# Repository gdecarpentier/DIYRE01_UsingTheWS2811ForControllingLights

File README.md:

# DIYRE01_UsingTheWS2811ForControllingLights

Repository of the free source code and schematics accompanying this YouTube video:

[DIY Railway Electronics # 01 - Using the WS2811 for controlling lights](https://www.youtube.com/watch?v=AYqMWdDcELc).

|Directory|Description|
|-|-|
| /ws2811_eagle | The EAGLE schematics and board files for the WS2811 board in the video. |
| /ws2811_arduino | Arduino project. Relay light values it receives over its (USB) COM port to all connected WS2811 chips.|
| /ws2811_python | Python project. Updates and sends (building & dome) light values over a (USB) COM port continously. |

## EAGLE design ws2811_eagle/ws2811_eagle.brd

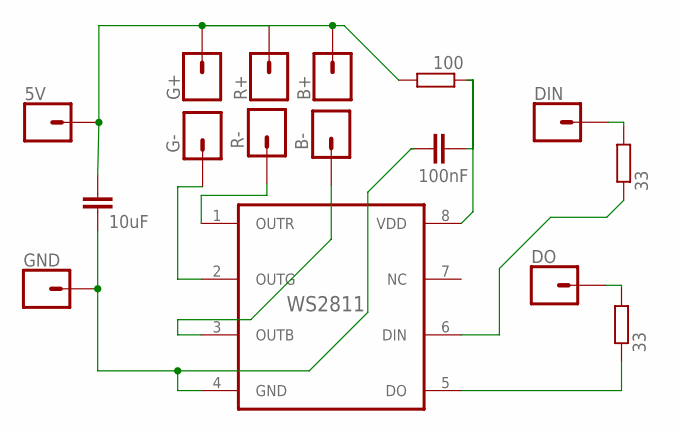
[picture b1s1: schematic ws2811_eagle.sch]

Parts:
5V: 1PIN; 1PIN_1.0MMCORE
B+: 1PIN1PIN_0.8MMCORE; 1PIN_0.8MMCORE
B-: 1PIN1PIN_0.8MMCORE; 1PIN_0.8MMCORE
C1: 10uF; C0805; VOLTAGERATING 10+ V
C2: 100nF; C0805; VOLTAGERATING 10+ V
DIN: 1PIN; 1PIN_1.0MMCORE
DO: 1PIN; 1PIN_1.0MMCORE
G+: 1PIN1PIN_0.8MMCORE; 1PIN_0.8MMCORE
G-: 1PIN1PIN_0.8MMCORE; 1PIN_0.8MMCORE
GND: 1PIN; 1PIN_1.0MMCORE
R1, R3: 33; R0805
R2: 100; R0805
R+: 1PIN1PIN_0.8MMCORE; 1PIN_0.8MMCORE
R-: 1PIN1PIN_0.8MMCORE; 1PIN_0.8MMCORE
WS2811: WS2811; SO08

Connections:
unnamed: C2.2, R2.1, WS2811.8 (VDD)
unnamed: C1.2, C2.1, GND.1, WS2811.4 (GND)
unnamed: R1.1, WS2811.6 (DIN)
unnamed: DIN.1, R1.2
unnamed: R-.1, WS2811.1 (OUTR)
unnamed: G-.1, WS2811.2 (OUTG)
unnamed: B-.1, WS2811.3 (OUTB)
unnamed: R3.1, WS2811.5 (DO)
unnamed: 5V.1, B+.1, C1.1, G+.1, R2.2, R+.1
unnamed: DO.1, R3.2

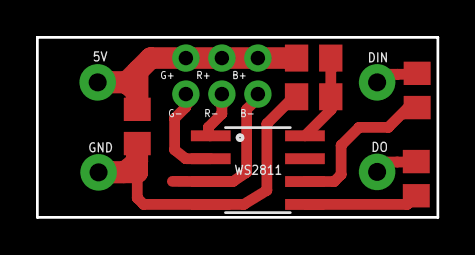
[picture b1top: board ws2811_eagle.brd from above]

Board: 2 copper layers, 22.2 x 10.0 mm, 16 parts (0 on the bottom side), 10 nets.

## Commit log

2021-09-09 Documentation, source code and board schematics
2021-09-09 Fixed broken link in documentation
2021-09-09 Fixed broken link in documentation again
